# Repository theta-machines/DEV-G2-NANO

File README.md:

# G2 Nano Development Board
This repository houses the KiCad source files for the G2 Nano microcontroller development board.

The G2 Nano is powered by a record-breaking 1 GHz Arm Cortex-M7 processor, combining the performance of an application processor with real-time determinism. Purpose-built for robotics R&D, the board integrates dual-band Wi-Fi, an inertial measurement unit, and an on-board closed-loop motion controller.

## Overview
* This PCB was designed using KiCad 10 and it's standard library of components.

* The KiCad project is contained within the `kicad/` directory and can be opened via the `kicad/DEV-G2-NANO.kicad_pro` file.

* All custom symbols and footprints are located in the `kicad/project_lib/` directory. The same directory houses the schematic page template.

## Features
### Performance
* 1 GHz Arm Cortex-M7 Microprocessor
* Double-Precision Floating Point Unit
* 2 MiB RAM (512 KiB Tightly Coupled)
* 8 MiB QSPI Flash Memory
* Cryptographic Acceleration (Including Random Number Generation)
* Two 32-Channel DMA Engines

### Peripherals
* Dual-Band Wi-Fi
* 6-Axis IMU (3-Axis Accelerometer; 3-Axis Gyroscope)
* 3-Axis Magnetometer
* 3-Axis Closed-Loop Motion Controller <!-- TODO: provide link to part -->
* Real-Time Clock (Optionally powered with a coin cell battery)
* Built-In Hardware Debugger

### Digital I/O
* 40 Digital GPIO
* 2 CAN/CAN-FD Interfaces
* 3 I2C Interfaces
* 2 SPI Interfaces
* 5 UART Interfaces

### Analog & Audio
* 10 Analog Inputs
* 2 I2S/TDM Interfaces
* S/PDIF Interface

## Using This Project
*This section is an informal summary of the license. For the full terms, see the `LICENSE.txt` file.*

The design files in this repository are licensed under the *CERN Open Hardware Licence Version 2 - Permissive* (CERN-OHL-P-2.0).

You are free to:
* Study these files and use them as inspiration or reference for your own independently created designs. As long as you are not copying, modifying, or redistributing the licensed design files, then you are not required to give attribution or license your design under the same terms.

* Copy, modify, and redistribute these files, including under different terms, provided you comply with the CERN-OHL-P-2.0 requirements.

**Trademarks:** No trademark rights are granted under this license. You may not use any trademarks or logos owned by Theta Machines LLC to endorse or promote products or services without prior written permission.

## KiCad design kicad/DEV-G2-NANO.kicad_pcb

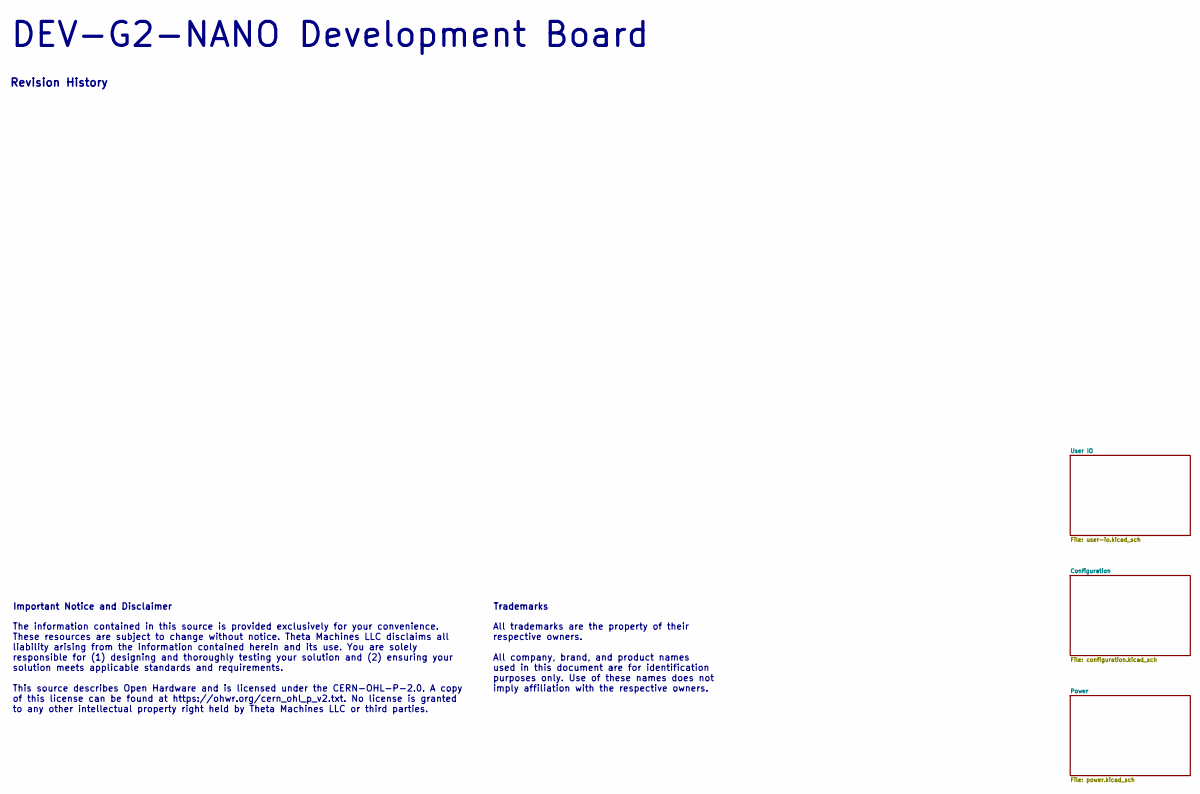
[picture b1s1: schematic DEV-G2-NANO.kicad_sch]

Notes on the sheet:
Revision History
DEV-G2-NANO Development Board
Important Notice and Disclaimer
Trademarks
The information contained in this source is provided exclusively for your convenience. These resources are subject to change without notice. Theta Machines LLC disclaims all liability arising from the information contained herein and its use. You are solely responsible for (1) designing and thoroug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
All trademarks are the property of their respective owners. All company, brand, and product names used in this document are for identification purposes only. Use of these names does not imply affiliation with the respective owners.

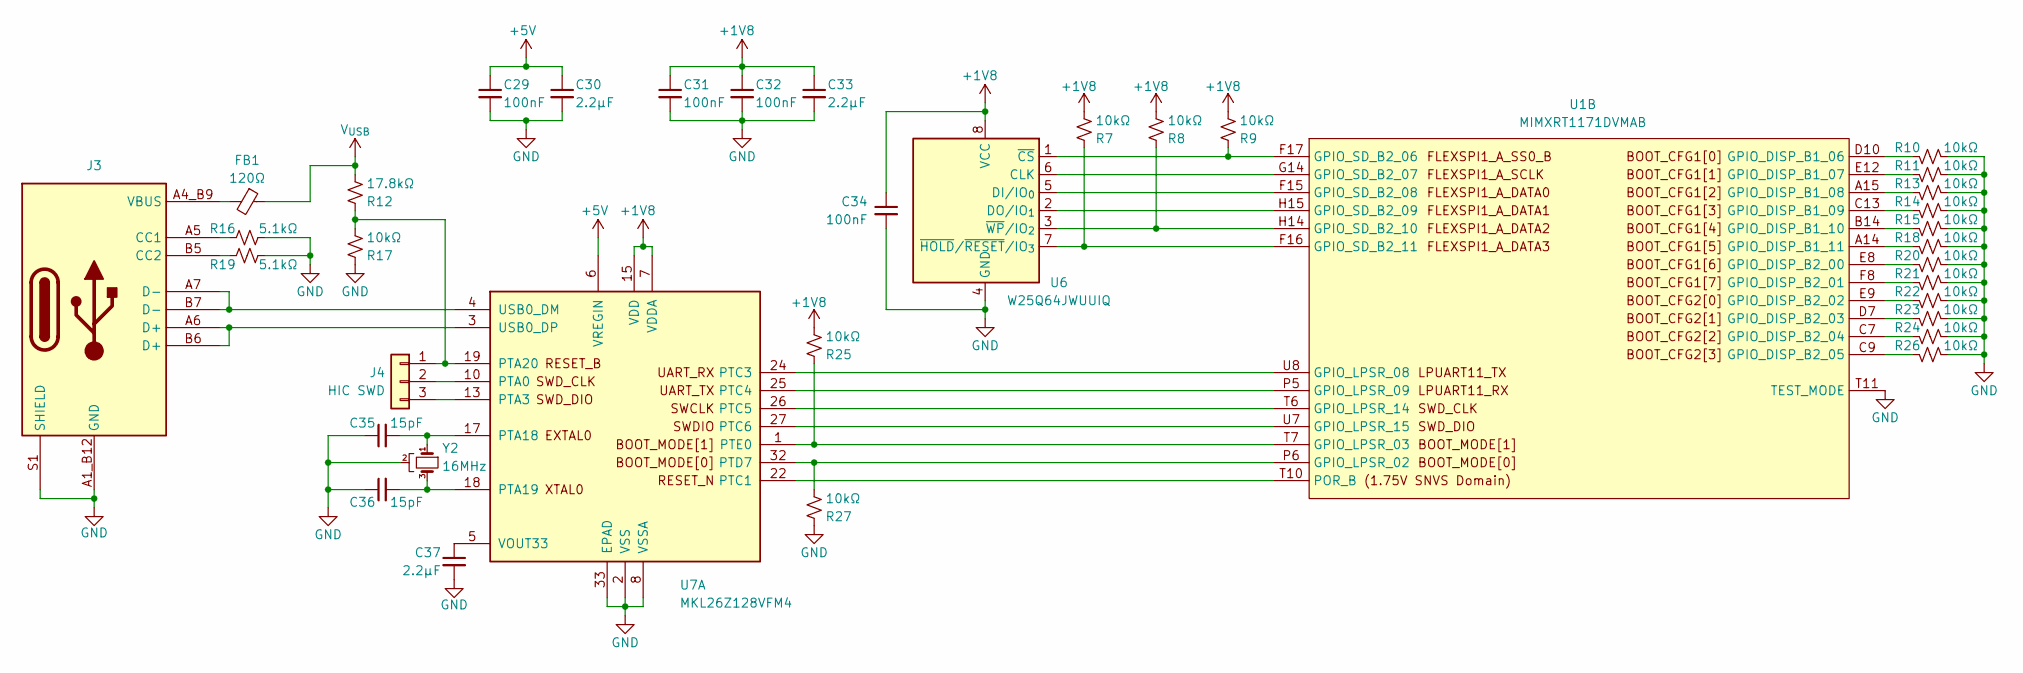
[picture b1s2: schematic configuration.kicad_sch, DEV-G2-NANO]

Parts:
C29, C31, C32, C34: 100nF; C_0201_0603Metric
C30, C33, C37: 2.2μF; C_0201_0603Metric
C35, C36: 15pF; C_0402_1005Metric
FB1: 120Ω; L_0402_1005Metric
J3: USB C; UJ20-C-H-G-SMT-5-P16
J4: HIC SWD; TestPoints-3
R7, R8, R9, R10, R11, R13, R14, R15, R17, R18, R20, R21, R22, R23, R24, R25, R26, R27: 10kΩ; R_0201_0603Metric
R12: 17.8kΩ; R_0201_0603Metric
R16, R19: 5.1kΩ; R_0201_0603Metric
U1: MIMXRT1171DVMAB
U6: W25Q64JWUUIQ
U7: MKL26Z128VFM4
Y2: 16MHz; Crystal-4-Pin

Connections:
+1V8: C31.1, C32.1, C33.1, C34.1, R7.2, R8.2, R9.2, R25.2, U6.8 (VCC), U7.7 (VDDA), U7.15 (VDD); also elsewhere on the board
+5V: C29.1, C30.1, U7.6 (VREGIN); also elsewhere on the board
GND: C29.2, C30.2, C31.2, C32.2, C33.2, C34.2, C35.1, C36.1, C37.2, J3.A1_B12 (GND), J3.B1_A12 (GND), J3.S1 (SHIELD), R10.2, R11.2, R13.2, R14.2, R15.2, R16.2, R17.1, R18.2, R19.2, R20.2, R21.2, R22.2, R23.2, R24.2, R26.2, R27.1, U1.T11 (TEST_MODE), U6.4 (GND), U7.2 (VSS), U7.8 (VSSA), U7.16 (VSS), U7.33 (EPAD), Y2.2 (GND), Y2.4 (GND); also elsewhere on the board
unnamed: FB1.2, J3.A4_B9 (VBUS), J3.B4_A9 (VBUS)
unnamed: J3.A5 (CC1), R16.1
unnamed: J3.B5 (CC2), R19.1
unnamed: J4.1, R12.1, R17.2, U7.19 (PTA20)
unnamed: J4.2, U7.10 (PTA0)
unnamed: J4.3, U7.13 (PTA3)
unnamed: R10.1, U1.D10 (GPIO_DISP_B1_06)
unnamed: R11.1, U1.E12 (GPIO_DISP_B1_07)
unnamed: R13.1, U1.A15 (GPIO_DISP_B1_08)
unnamed: R14.1, U1.C13 (GPIO_DISP_B1_09)
unnamed: R15.1, U1.B14 (GPIO_DISP_B1_10)
unnamed: R18.1, U1.A14 (GPIO_DISP_B1_11)
unnamed: R20.1, U1.E8 (GPIO_DISP_B2_00)
unnamed: R21.1, U1.F8 (GPIO_DISP_B2_01)
unnamed: R22.1, U1.E9 (GPIO_DISP_B2_02)
unnamed: R23.1, U1.D7 (GPIO_DISP_B2_03)
unnamed: R24.1, U1.C7 (GPIO_DISP_B2_04)
unnamed: R26.1, U1.C9 (GPIO_DISP_B2_05)
unnamed: R27.2, U1.P6 (GPIO_LPSR_02), U7.32 (PTD7)
unnamed: R25.1, U1.T7 (GPIO_LPSR_03), U7.1 (PTE0)
unnamed: U1.U8 (GPIO_LPSR_08), U7.24 (PTC3)
unnamed: U1.P5 (GPIO_LPSR_09), U7.25 (PTC4)
unnamed: U1.T6 (GPIO_LPSR_14), U7.26 (PTC5)
unnamed: U1.U7 (GPIO_LPSR_15), U7.27 (PTC6)
unnamed: R9.1, U1.F17 (GPIO_SD_B2_06), U6.1 (~CS)
unnamed: U1.G14 (GPIO_SD_B2_07), U6.6 (CLK)
unnamed: U1.F15 (GPIO_SD_B2_08), U6.5 (DI/IO_{0})
unnamed: U1.H15 (GPIO_SD_B2_09), U6.2 (DO/IO_{1})
unnamed: R8.1, U1.H14 (GPIO_SD_B2_10), U6.3 (~WP/IO_{2})
unnamed: R7.1, U1.F16 (GPIO_SD_B2_11), U6.7 (~HOLD/~RESET/IO_{3})
unnamed: U1.T10 (POR_B), U7.22 (PTC1)
unnamed: C35.2, U7.17 (PTA18), Y2.1
unnamed: C36.2, U7.18 (PTA19), Y2.3
unnamed: J3.A7 (D-), J3.B7 (D-), U7.4 (USB0_DM)
unnamed: J3.A6 (D+), J3.B6 (D+), U7.3 (USB0_DP)
unnamed: C37.1, U7.5 (VOUT33)
V_{USB}: FB1.1, R12.2; also elsewhere on the board

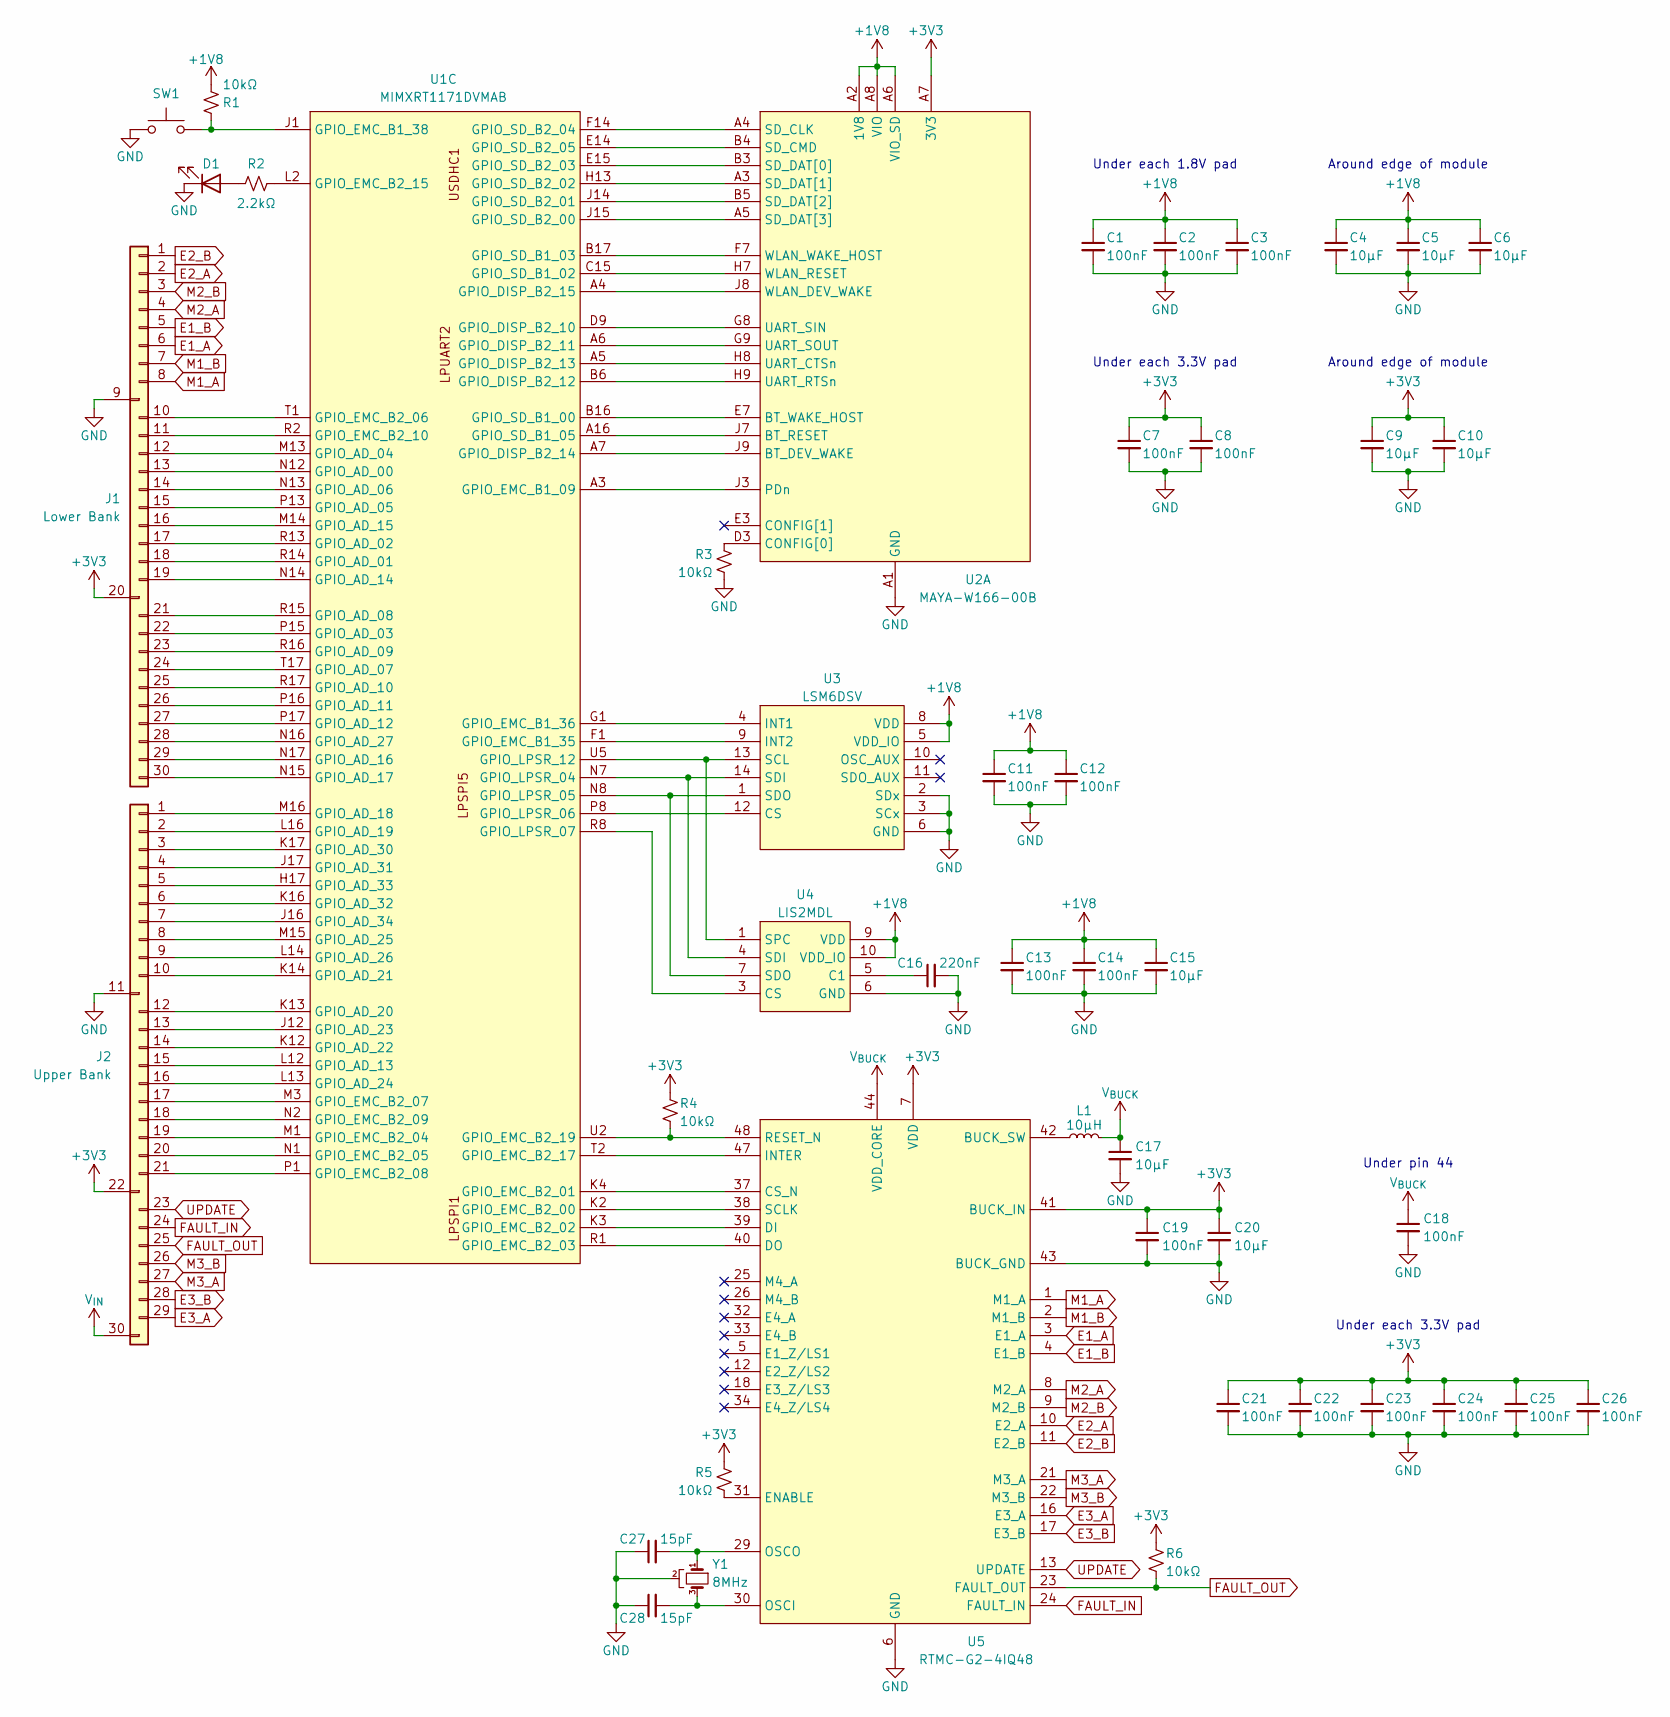
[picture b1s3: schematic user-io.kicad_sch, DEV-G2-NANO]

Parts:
C1, C2, C3, C7, C8, C11, C12, C13, C14, C18, C19, C21, C22, C23, C24, C25, C26: 100nF; C_0201_0603Metric
C4, C5, C6, C9, C10, C15, C17, C20: 10μF; C_0402_1005Metric
C16: 220nF; C_0201_0603Metric
C27, C28: 15pF; C_0402_1005Metric
D1: RED; LED_0603_1608Metric
J1: Lower Bank; Header-1x30
J2: Upper Bank; Header-1x30
L1: 10μH; L_1008_2520Metric
R1, R3, R4, R5, R6: 10kΩ; R_0201_0603Metric
R2: 2.2kΩ; R_0201_0603Metric
SW1: PTS815
U1: MIMXRT1171DVMAB
U2: MAYA-W166-00B
U3: LSM6DSV
U4: LIS2MDL
U5: RTMC-G2-4IQ48
Y1: 8MHz; Crystal-4-Pin

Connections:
+1V8: C1.1, C2.1, C3.1, C4.1, C5.1, C6.1, C11.1, C12.1, C13.1, C14.1, C15.1, R1.2, U2.A2 (1V8), U2.A6 (VIO_SD), U2.A8 (VIO), U3.5 (VDD_IO), U3.8 (VDD), U4.9 (VDD), U4.10 (VDD_IO); also elsewhere on the board
+3V3: C7.1, C8.1, C9.1, C10.1, C19.1, C20.1, C21.1, C22.1, C23.1, C24.1, C25.1, C26.1, J1.20, J2.22, R4.1, R5.1, R6.1, U2.A7 (3V3), U2.B7 (3V3), U5.7 (VDD), U5.15 (VDD), U5.20 (VDD), U5.28 (VDD), U5.36 (VDD), U5.41 (BUCK_IN), U5.46 (VDD); also elsewhere on the board
E1_A: J1.6, U5.3 (E1_A)
E1_B: J1.5, U5.4 (E1_B)
E2_A: J1.2, U5.10 (E2_A)
E2_B: J1.1, U5.11 (E2_B)
E3_A: J2.29, U5.16 (E3_A)
E3_B: J2.28, U5.17 (E3_B)
FAULT_IN: J2.24, U5.24 (FAULT_IN)
FAULT_OUT: J2.25, R6.2, U5.23 (FAULT_OUT)
GND: C1.2, C2.2, C3.2, C4.2, C5.2, C6.2, C7.2, C8.2, C9.2, C10.2, C11.2, C12.2, C13.2, C14.2, C15.2, C16.2, C17.2, C18.2, C19.2, C20.2, C21.2, C22.2, C23.2, C24.2, C25.2, C26.2, C27.1, C28.1, D1.1 (K), J1.9, J2.11, R3.2, SW1.1, U2.A1 (GND), U2.A9 (GND), U2.B2 (GND), U2.B8 (GND), U2.E4 (GND), U2.E5 (GND), U2.F4 (GND), U2.F5 (GND), U2.H4 (GND), U2.H5 (GND), U2.K2 (GND), U2.K3 (GND), U2.K4 (GND), U2.K6 (GND), U2.K7 (GND), U2.K8 (GND), U2.L1 (GND), U2.L9 (GND), U2.M1 (GND), U2.M2 (GND), U2.M8 (GND), U2.M9 (GND), U3.2 (SDx), U3.3 (SCx), U3.6 (GND), U3.7 (GND), U4.6 (GND), U4.8 (GND), U5.6 (GND), U5.14 (GND), U5.19 (GND), U5.27 (GND), U5.35 (GND), U5.43 (BUCK_GND), U5.45 (GND), Y1.2 (GND), Y1.4 (GND); also elsewhere on the board
M1_A: J1.8, U5.1 (M1_A)
M1_B: J1.7, U5.2 (M1_B)
M2_A: J1.4, U5.8 (M2_A)
M2_B: J1.3, U5.9 (M2_B)
M3_A: J2.27, U5.21 (M3_A)
M3_B: J2.26, U5.22 (M3_B)
unnamed: D1.2 (A), R2.1
unnamed: J1.10, U1.T1 (GPIO_EMC_B2_06)
unnamed: J1.11, U1.R2 (GPIO_EMC_B2_10)
unnamed: J1.12, U1.M13 (GPIO_AD_04)
unnamed: J1.13, U1.N12 (GPIO_AD_00)
unnamed: J1.14, U1.N13 (GPIO_AD_06)
unnamed: J1.15, U1.P13 (GPIO_AD_05)
unnamed: J1.16, U1.M14 (GPIO_AD_15)
unnamed: J1.17, U1.R13 (GPIO_AD_02)
unnamed: J1.18, U1.R14 (GPIO_AD_01)
unnamed: J1.19, U1.N14 (GPIO_AD_14)
unnamed: J1.21, U1.R15 (GPIO_AD_08)
unnamed: J1.22, U1.P15 (GPIO_AD_03)
unnamed: J1.23, U1.R16 (GPIO_AD_09)
unnamed: J1.24, U1.T17 (GPIO_AD_07)
unnamed: J1.25, U1.R17 (GPIO_AD_10)
unnamed: J1.26, U1.P16 (GPIO_AD_11)
unnamed: J1.27, U1.P17 (GPIO_AD_12)
unnamed: J1.28, U1.N16 (GPIO_AD_27)
unnamed: J1.29, U1.N17 (GPIO_AD_16)
unnamed: J1.30, U1.N15 (GPIO_AD_17)
unnamed: J2.1, U1.M16 (GPIO_AD_18)
unnamed: J2.2, U1.L16 (GPIO_AD_19)
unnamed: J2.3, U1.K17 (GPIO_AD_30)
unnamed: J2.4, U1.J17 (GPIO_AD_31)
unnamed: J2.5, U1.H17 (GPIO_AD_33)
unnamed: J2.6, U1.K16 (GPIO_AD_32)
unnamed: J2.7, U1.J16 (GPIO_AD_34)
unnamed: J2.8, U1.M15 (GPIO_AD_25)
unnamed: J2.9, U1.L14 (GPIO_AD_26)
unnamed: J2.10, U1.K14 (GPIO_AD_21)
unnamed: J2.12, U1.K13 (GPIO_AD_20)
unnamed: J2.13, U1.J12 (GPIO_AD_23)
unnamed: J2.14, U1.K12 (GPIO_AD_22)
unnamed: J2.15, U1.L12 (GPIO_AD_13)
unnamed: J2.16, U1.L13 (GPIO_AD_24)
unnamed: J2.17, U1.M3 (GPIO_EMC_B2_07)
unnamed: J2.18, U1.N2 (GPIO_EMC_B2_09)
unnamed: J2.19, U1.M1 (GPIO_EMC_B2_04)
unnamed: J2.20, U1.N1 (GPIO_EMC_B2_05)
unnamed: J2.21, U1.P1 (GPIO_EMC_B2_08)
unnamed: U1.D9 (GPIO_DISP_B2_10), U2.G8 (UART_SIN)
unnamed: U1.A6 (GPIO_DISP_B2_11), U2.G9 (UART_SOUT)
unnamed: U1.B6 (GPIO_DISP_B2_12), U2.H9 (UART_RTSn)
unnamed: U1.A5 (GPIO_DISP_B2_13), U2.H8 (UART_CTSn)
unnamed: U1.A7 (GPIO_DISP_B2_14), U2.J9 (BT_DEV_WAKE)
unnamed: U1.A4 (GPIO_DISP_B2_15), U2.J8 (WLAN_DEV_WAKE)
unnamed: U1.A3 (GPIO_EMC_B1_09), U2.J3 (PDn)
unnamed: U1.F1 (GPIO_EMC_B1_35), U3.9 (INT2)
unnamed: U1.G1 (GPIO_EMC_B1_36), U3.4 (INT1)
unnamed: R1.1, SW1.2, U1.J1 (GPIO_EMC_B1_38)
unnamed: U1.K2 (GPIO_EMC_B2_00), U5.38 (SCLK)
unnamed: U1.K4 (GPIO_EMC_B2_01), U5.37 (CS_N)
unnamed: U1.K3 (GPIO_EMC_B2_02), U5.39 (DI)
unnamed: U1.R1 (GPIO_EMC_B2_03), U5.40 (DO)
unnamed: R2.2, U1.L2 (GPIO_EMC_B2_15)
unnamed: U1.T2 (GPIO_EMC_B2_17), U5.47 (INTER)
unnamed: R4.2, U1.U2 (GPIO_EMC_B2_19), U5.48 (RESET_N)
unnamed: U1.N7 (GPIO_LPSR_04), U3.14 (SDI), U4.4 (SDI)
unnamed: U1.N8 (GPIO_LPSR_05), U3.1 (SDO), U4.7 (SDO)
unnamed: U1.P8 (GPIO_LPSR_06), U3.12 (CS)
unnamed: U1.R8 (GPIO_LPSR_07), U4.3 (CS)
unnamed: U1.U5 (GPIO_LPSR_12), U3.13 (SCL), U4.1 (SPC)
unnamed: U1.B16 (GPIO_SD_B1_00), U2.E7 (BT_WAKE_HOST)
unnamed: U1.C15 (GPIO_SD_B1_02), U2.H7 (WLAN_RESET)
unnamed: U1.B17 (GPIO_SD_B1_03), U2.F7 (WLAN_WAKE_HOST)
unnamed: U1.A16 (GPIO_SD_B1_05), U2.J7 (BT_RESET)
unnamed: U1.J15 (GPIO_SD_B2_00), U2.A5 (SD_DAT[3])
unnamed: U1.J14 (GPIO_SD_B2_01), U2.B5 (SD_DAT[2])
unnamed: U1.H13 (GPIO_SD_B2_02), U2.A3 (SD_DAT[1])
unnamed: U1.E15 (GPIO_SD_B2_03), U2.B3 (SD_DAT[0])
unnamed: U1.F14 (GPIO_SD_B2_04), U2.A4 (SD_CLK)
unnamed: U1.E14 (GPIO_SD_B2_05), U2.B4 (SD_CMD)
unnamed: R3.1, U2.D3 (CONFIG[0])
unnamed: C16.1, U4.5 (C1)
unnamed: L1.2, U5.42 (BUCK_SW)
unnamed: R5.2, U5.31 (ENABLE)
unnamed: C28.2, U5.30 (OSCI), Y1.3
unnamed: C27.2, U5.29 (OSCO), Y1.1
UPDATE: J2.23, U5.13 (UPDATE)
V_{BUCK}: C17.1, C18.1, L1.1, U5.44 (VDD_CORE)
V_{IN}: J2.30; also elsewhere on the board

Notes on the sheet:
Under each 1.8V pad
Around edge of module
Under each 3.3V pad
Under pin 44

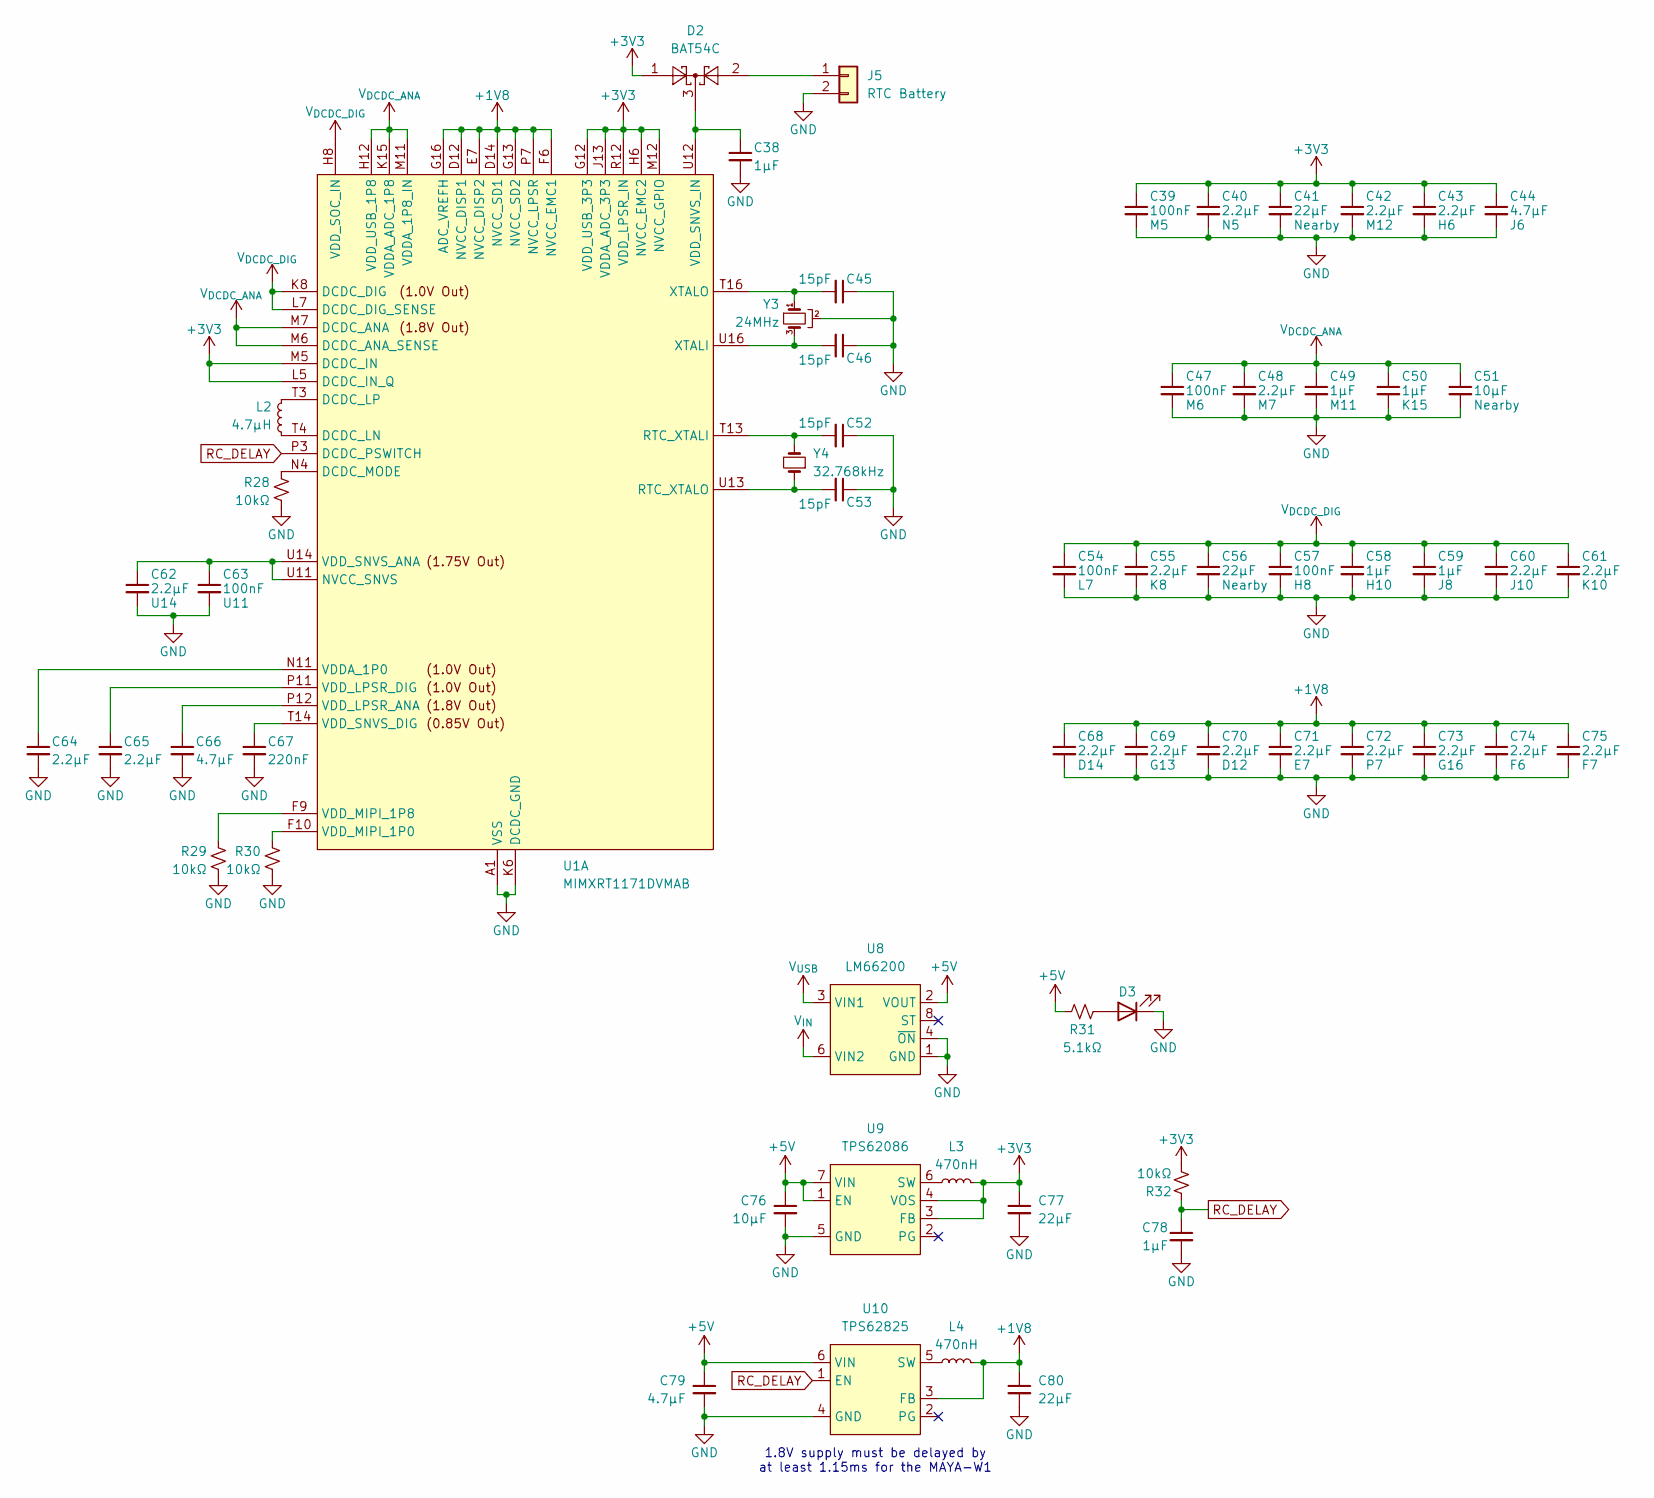
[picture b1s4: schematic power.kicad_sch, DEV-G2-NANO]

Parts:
C38, C49, C50, C58, C59, C78: 1μF; C_0201_0603Metric
C39, C47, C54, C57, C63: 100nF; C_0201_0603Metric
C40, C42, C43, C48, C55, C60, C61, C62, C64, C65, C68, C69, C70, C71, C72, C73, C74, C75: 2.2μF; C_0201_0603Metric
C41, C56, C77, C80: 22μF; C_0603_1608Metric
C44, C66, C79: 4.7μF; C_0402_1005Metric
C45, C46, C52, C53: 15pF; C_0402_1005Metric
C51, C76: 10μF; C_0402_1005Metric
C67: 220nF; C_0201_0603Metric
D2: BAT54C
D3: RED; LED_0603_1608Metric
J5: RTC Battery; Header-1x02
L2: 4.7μH; SDCL1V4018
L3, L4: 470nH; L_0806
R28, R29, R30, R32: 10kΩ; R_0201_0603Metric
R31: 5.1kΩ; R_0201_0603Metric
U1: MIMXRT1171DVMAB
U8: LM66200
U9: TPS62086
U10: TPS62825
Y3: 24MHz; Crystal-4-Pin
Y4: 32.768kHz; Crystal-2-Pin

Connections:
+1V8: C68.1, C69.1, C70.1, C71.1, C72.1, C73.1, C74.1, C75.1, C80.1, L4.2, U1.D12 (NVCC_DISP1), U1.D14 (NVCC_SD1), U1.E7 (NVCC_DISP2), U1.F6 (NVCC_EMC1), U1.F7 (NVCC_EMC1), U1.G6 (NVCC_EMC1), U1.G13 (NVCC_SD2), U1.G16 (ADC_VREFH), U1.P7 (NVCC_LPSR), U10.3 (FB); also elsewhere on the board
+3V3: C39.1, C40.1, C41.1, C42.1, C43.1, C44.1, C77.1, D2.1, L3.2, R32.2, U1.G12 (VDD_USB_3P3), U1.H6 (NVCC_EMC2), U1.J6 (NVCC_EMC2), U1.J13 (VDDA_ADC_3P3), U1.L5 (DCDC_IN_Q), U1.M5 (DCDC_IN), U1.M12 (NVCC_GPIO), U1.N5 (DCDC_IN), U1.R12 (VDD_LPSR_IN), U9.3 (FB), U9.4 (VOS); also elsewhere on the board
+5V: C76.1, C79.1, R31.1, U8.2 (VOUT), U8.7 (VOUT), U9.1 (EN), U9.7 (VIN), U10.6 (VIN); also elsewhere on the board
GND: C38.2, C39.2, C40.2, C41.2, C42.2, C43.2, C44.2, C45.1, C46.1, C47.2, C48.2, C49.2, C50.2, C51.2, C52.1, C53.1, C54.2, C55.2, C56.2, C57.2, C58.2, C59.2, C60.2, C61.2, C62.2, C63.2, C64.2, C65.2, C66.2, C67.2, C68.2, C69.2, C70.2, C71.2, C72.2, C73.2, C74.2, C75.2, C76.2, C77.2, C78.2, C79.2, C80.2, D3.1 (K), J5.2, R28.2, R29.2, R30.2, U1.A1 (VSS), U1.A17 (VSS), U1.B7 (VSS), U1.C8 (VSS), U1.C10 (VSS), U1.C12 (VSS), U1.C14 (VSS), U1.D4 (VSS), U1.F11 (VSS), U1.F12 (VSS), U1.F13 (VSS), U1.G3 (VSS), U1.G7 (VSS), U1.G8 (VSS), U1.G9 (VSS), U1.G10 (VSS), U1.G11 (VSS), U1.G15 (VSS), U1.H7 (VSS), U1.H11 (VSS), U1.J7 (VSS), U1.J11 (VSS), U1.K6 (DCDC_GND), U1.K7 (DCDC_GND), U1.K11 (VSS), U1.L3 (VSS), U1.L6 (DCDC_GND), U1.L10 (VSS), U1.L11 (VSS), U1.L15 (VSS), U1.P4 (VSS), U1.P14 (VSS), U1.R4 (VSS), U1.R7 (VSS), U1.T12 (VSS), U1.U1 (VSS), U1.U17 (VSS), U8.1 (GND), U8.4 (~ON), U8.5 (GND), U9.5 (GND), U10.4 (GND), Y3.2 (GND), Y3.4 (GND); also elsewhere on the board
unnamed: D3.2 (A), R31.2
unnamed: D2.2, J5.1
unnamed: L2.1, U1.T4 (DCDC_LN), U1.U4 (DCDC_LN)
unnamed: L2.2, U1.T3 (DCDC_LP), U1.U3 (DCDC_LP)
unnamed: R28.1, U1.N4 (DCDC_MODE)
unnamed: C62.1, C63.1, U1.U11 (NVCC_SNVS), U1.U14 (VDD_SNVS_ANA)
unnamed: C52.2, U1.T13 (RTC_XTALI), Y4.2
unnamed: C53.2, U1.U13 (RTC_XTALO), Y4.1
unnamed: C64.1, U1.N11 (VDDA_1P0)
unnamed: C66.1, U1.P12 (VDD_LPSR_ANA)
unnamed: C65.1, U1.P11 (VDD_LPSR_DIG)
unnamed: R30.1, U1.F10 (VDD_MIPI_1P0)
unnamed: R29.1, U1.F9 (VDD_MIPI_1P8)
unnamed: C67.1, U1.T14 (VDD_SNVS_DIG)
unnamed: C38.1, D2.3, U1.U12 (VDD_SNVS_IN)
unnamed: C46.2, U1.U16 (XTALI), Y3.3
unnamed: C45.2, U1.T16 (XTALO), Y3.1
unnamed: L3.1, U9.6 (SW)
unnamed: L4.1, U10.5 (SW)
RC_DELAY: C78.1, R32.1, U1.P3 (DCDC_PSWITCH), U10.1 (EN)
V_{DCDC_ANA}: C47.1, C48.1, C49.1, C50.1, C51.1, U1.H12 (VDD_USB_1P8), U1.K15 (VDDA_ADC_1P8), U1.M6 (DCDC_ANA_SENSE), U1.M7 (DCDC_ANA), U1.M8 (DCDC_ANA), U1.M11 (VDDA_1P8_IN)
V_{DCDC_DIG}: C54.1, C55.1, C56.1, C57.1, C58.1, C59.1, C60.1, C61.1, U1.H8 (VDD_SOC_IN), U1.H9 (VDD_SOC_IN), U1.H10 (VDD_SOC_IN), U1.J8 (VDD_SOC_IN), U1.J9 (VDD_SOC_IN), U1.J10 (VDD_SOC_IN), U1.K8 (DCDC_DIG), U1.K9 (DCDC_DIG), U1.K10 (VDD_SOC_IN), U1.L7 (DCDC_DIG_SENSE), U1.L8 (DCDC_DIG)
V_{IN}: U8.6 (VIN2); also elsewhere on the board
V_{USB}: U8.3 (VIN1); also elsewhere on the board

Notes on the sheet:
1.8V supply must be delayed by at least 1.15ms for the MAYA-W1

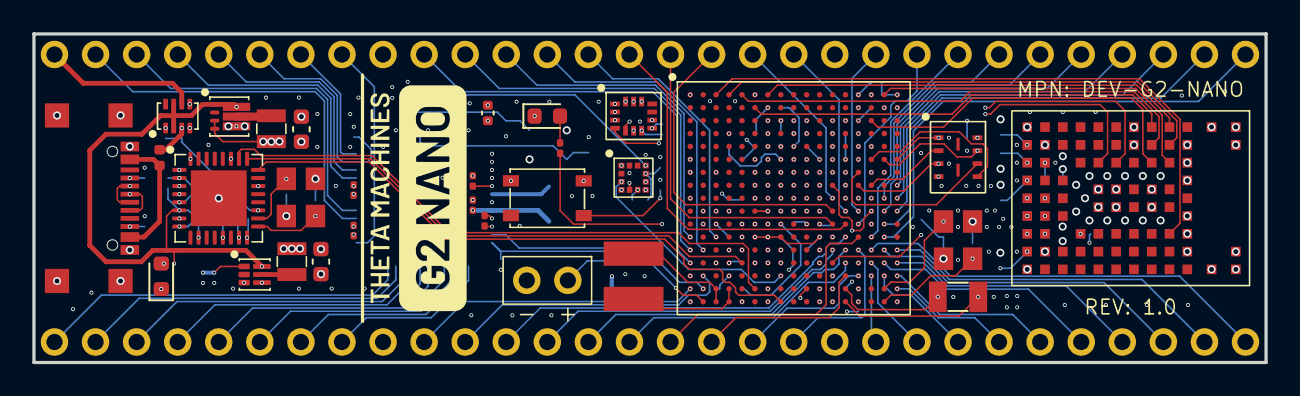
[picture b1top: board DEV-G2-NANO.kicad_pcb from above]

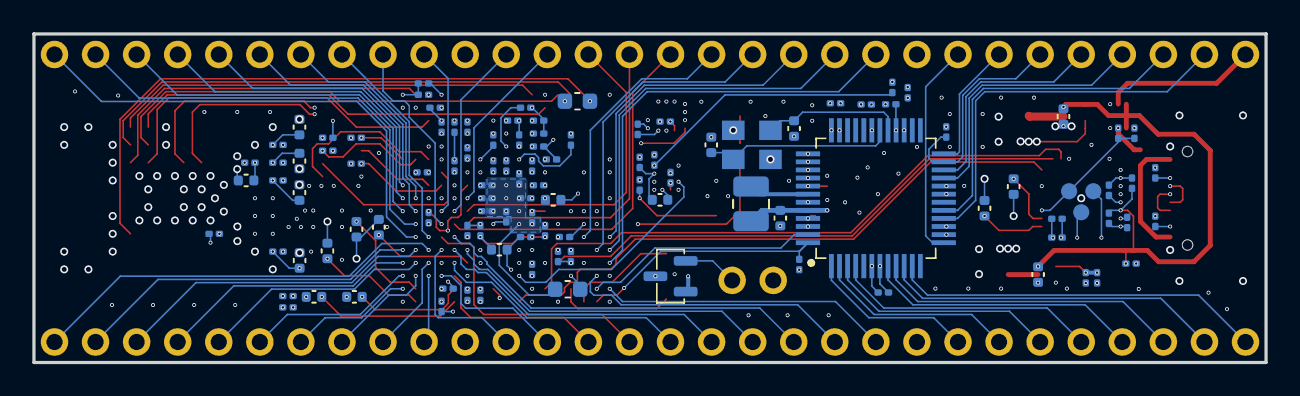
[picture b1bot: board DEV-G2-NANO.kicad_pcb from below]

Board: 6 copper layers, 76.2 x 20.3 mm, 140 parts (110 on the bottom side), 159 nets.

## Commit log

2026-04-18 added LICENSE.txt
2026-04-18 created KiCad project
2026-04-18 added README.md
2026-04-19 added feature list to README.md
2026-04-19 added MIMXRT1171DVMAB symbol to project
2026-04-20 added boot config and flash chip
2026-04-20 broke up MIMXRT1171DVMAB into several units
2026-04-20 organized schematic into several sheets
2026-04-24 added MAYA-W166-00B symbol
2026-04-25 reworked design to use 1.8V logic
2026-04-25 created footprint for Wi-Fi module (MAYA-W166)
2026-04-26 documented SDIO pull resistors
2026-04-26 added user button and LED
2026-04-26 added 3.3V and 1.8V buck converters to schematic
2026-04-26 added IMU to schematic
2026-04-26 added magnetometer to schematic
2026-04-26 added bypass caps
2026-04-27 added KL26 (DAPLink HIC) to schematic
2026-04-27 updated feature list
2026-04-29 added RTMC-G2-4IQ48 to schematic
2026-04-29 added several footprints
2026-04-30 added RTC battery connector
2026-04-30 centered TestPoints-3 footprint
2026-04-30 added crystal footprints
2026-04-30 added inductor footprints
2026-04-30 reworked bypass capacitors for MIMXRT1171DVMAB
2026-04-30 moved ADC_VREFH to +1V8 rail
2026-05-01 added ferrite beads to VDD_USB_xxx pins
2026-05-01 reworked USB circuitry
2026-05-02 added remaining footprints
2026-05-02 finished preliminary layout
2026-05-02 added rendering to README.md
2026-05-02 removed USB host and 1.8V DAC
2026-05-02 set PCB design rules
2026-05-04 updated .gitignore to exclude .history_trim/
2026-05-04 updated footprints
2026-05-06 finished preliminary routing
2026-05-06 added stitching vias and made cosmetic changes
2026-05-07 removed 3D models from project_lib
2026-05-07 updated rendering
2026-05-07 added solder paste to footprint
2026-05-12 added pull-up resistors to W25Q QSPI line
2026-06-29 cosmetic changes

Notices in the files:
kicad/DEV-G2-NANO.kicad_sch:
© 2026, Theta Machines LLC.
This source describes Open Hardware and is licensed under the CERN-OHL-P-2.0. A copy of this license can be found at https://ohwr.org/cern_ohl_p_v2.txt. No license is granted to any other intellectual property right held by Theta Machines LLC or third parties.
